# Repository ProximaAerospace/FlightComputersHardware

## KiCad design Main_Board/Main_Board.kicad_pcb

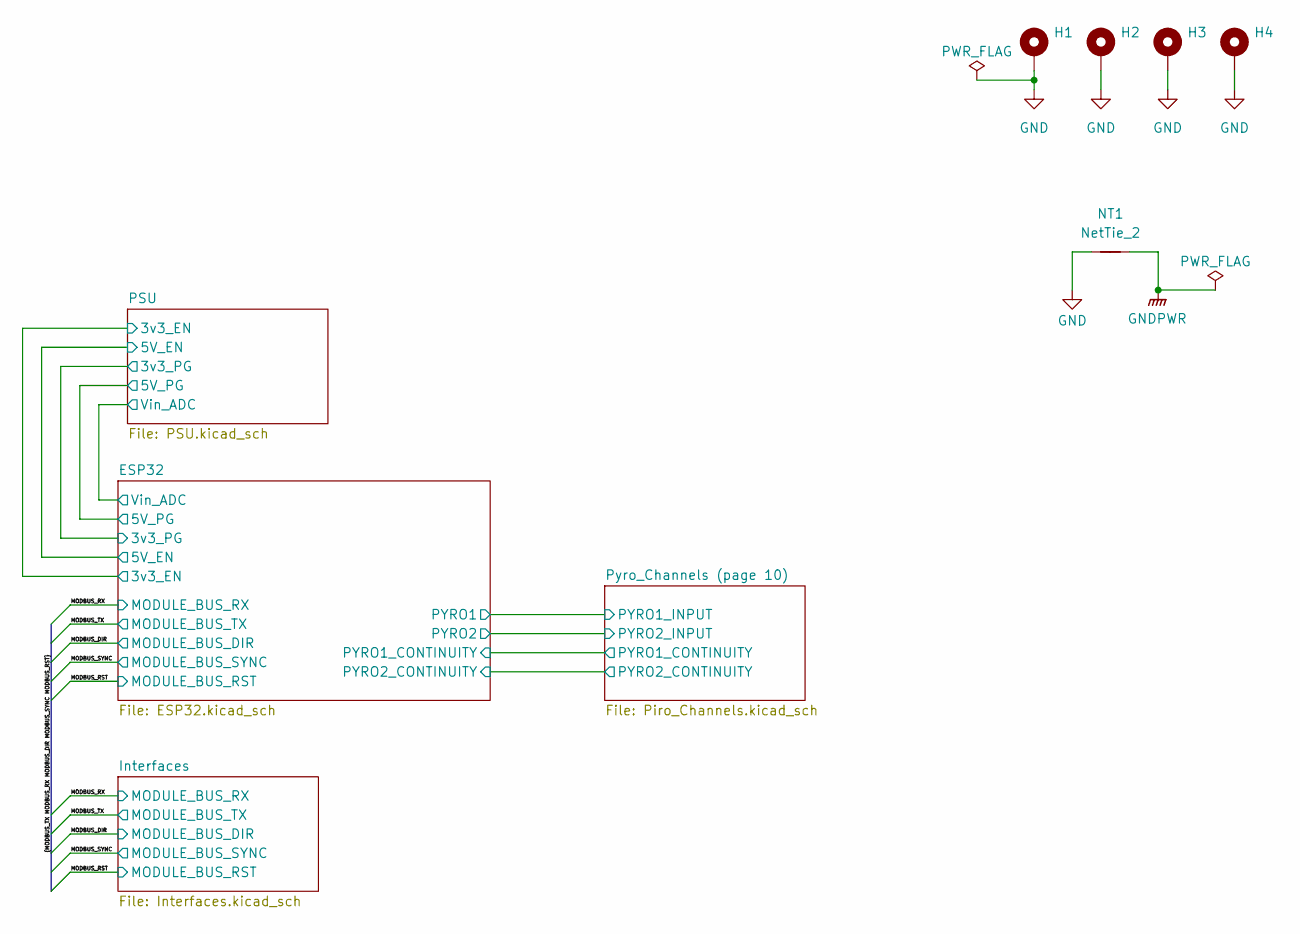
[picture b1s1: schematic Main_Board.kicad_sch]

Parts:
H1, H2: MountingHole_Pad; MountingHole_3.2mm_M3_DIN965_Pad_TopBottom
H3, H4: MountingHole_Pad; MountingHole_2.2mm_M2
NT1: NetTie_2; NetTie-2_SMD_Pad2.0mm

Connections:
GND: H1.1 (1_1), H2.1 (1_1), H3.1, H4.1, NT1.1; also elsewhere on the board
GNDPWR: NT1.2; also elsewhere on the board

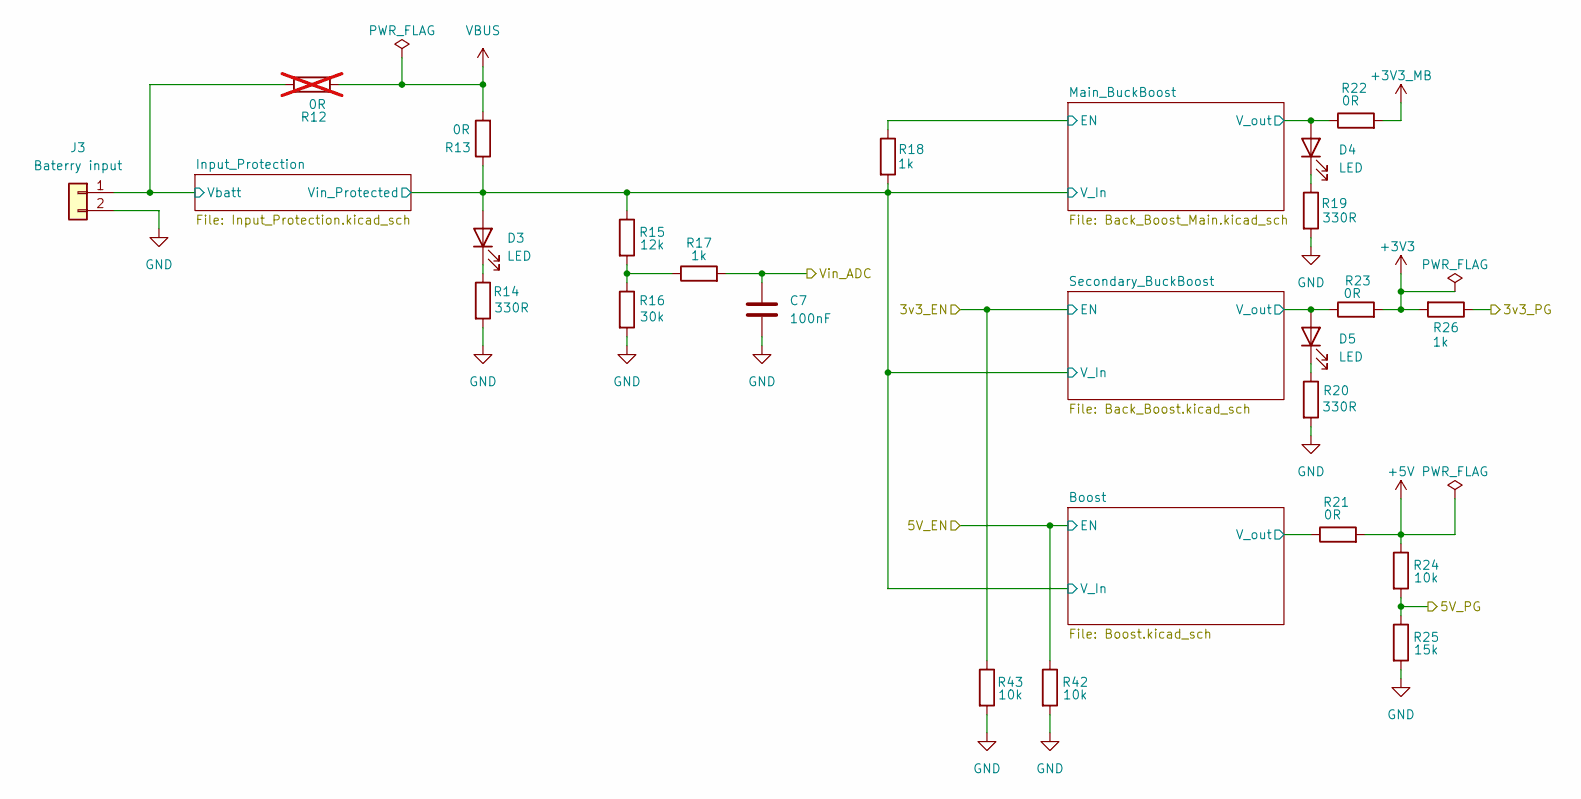
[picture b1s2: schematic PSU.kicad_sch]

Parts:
C7: 100nF; C_0603_1608Metric
D3, D4, D5: LED; D_0603_1608Metric
J3: Baterry input; JST_PH_B2B-PH-K_1x02_P2.00mm_Vertical
R12: 0R; R_0603_1608Metric; not fitted
R13: 0R; R_0805_2012Metric
R14, R19, R20: 330R; R_0603_1608Metric
R15: 12k; R_0603_1608Metric
R16: 30k; R_0603_1608Metric
R17, R18, R26: 1k; R_0603_1608Metric
R21, R22, R23: 0R; R_0603_1608Metric
R24, R42, R43: 10k; R_0603_1608Metric
R25: 15k; R_0603_1608Metric

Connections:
+3V3: R23.2, R26.2; also elsewhere on the board
+3V3_MB: R22.2; also elsewhere on the board
+5V: R21.2, R24.1; also elsewhere on the board
/ESP32/3v3_EN: R43.1; also elsewhere on the board
/ESP32/3v3_PG: R26.1; also elsewhere on the board
/ESP32/5V_EN: R42.1; also elsewhere on the board
/ESP32/5V_PG: R24.2, R25.1; also elsewhere on the board
/ESP32/Vin_ADC: C7.1, R17.2; also elsewhere on the board
/PSU/Boost/V_In: D3.2 (A), R13.1, R15.1, R18.2; also elsewhere on the board
/PSU/Boost/V_out: R21.1; also elsewhere on the board
/PSU/Input_Protection/Vbatt: J3.1, R12.2; also elsewhere on the board
/PSU/Main_BuckBoost/EN: R18.1; also elsewhere on the board
/PSU/Main_BuckBoost/V_out: D4.2 (A), R22.1; also elsewhere on the board
/PSU/Secondary_BuckBoost/V_out: D5.2 (A), R23.1; also elsewhere on the board
GND: C7.2, J3.2, R14.2, R16.2, R19.2, R20.2, R25.2, R42.2, R43.2; also elsewhere on the board
unnamed: D3.1 (K), R14.1
unnamed: D4.1 (K), R19.1
unnamed: D5.1 (K), R20.1
unnamed: R15.2, R16.1, R17.1
VBUS: R12.1, R13.2; also elsewhere on the board

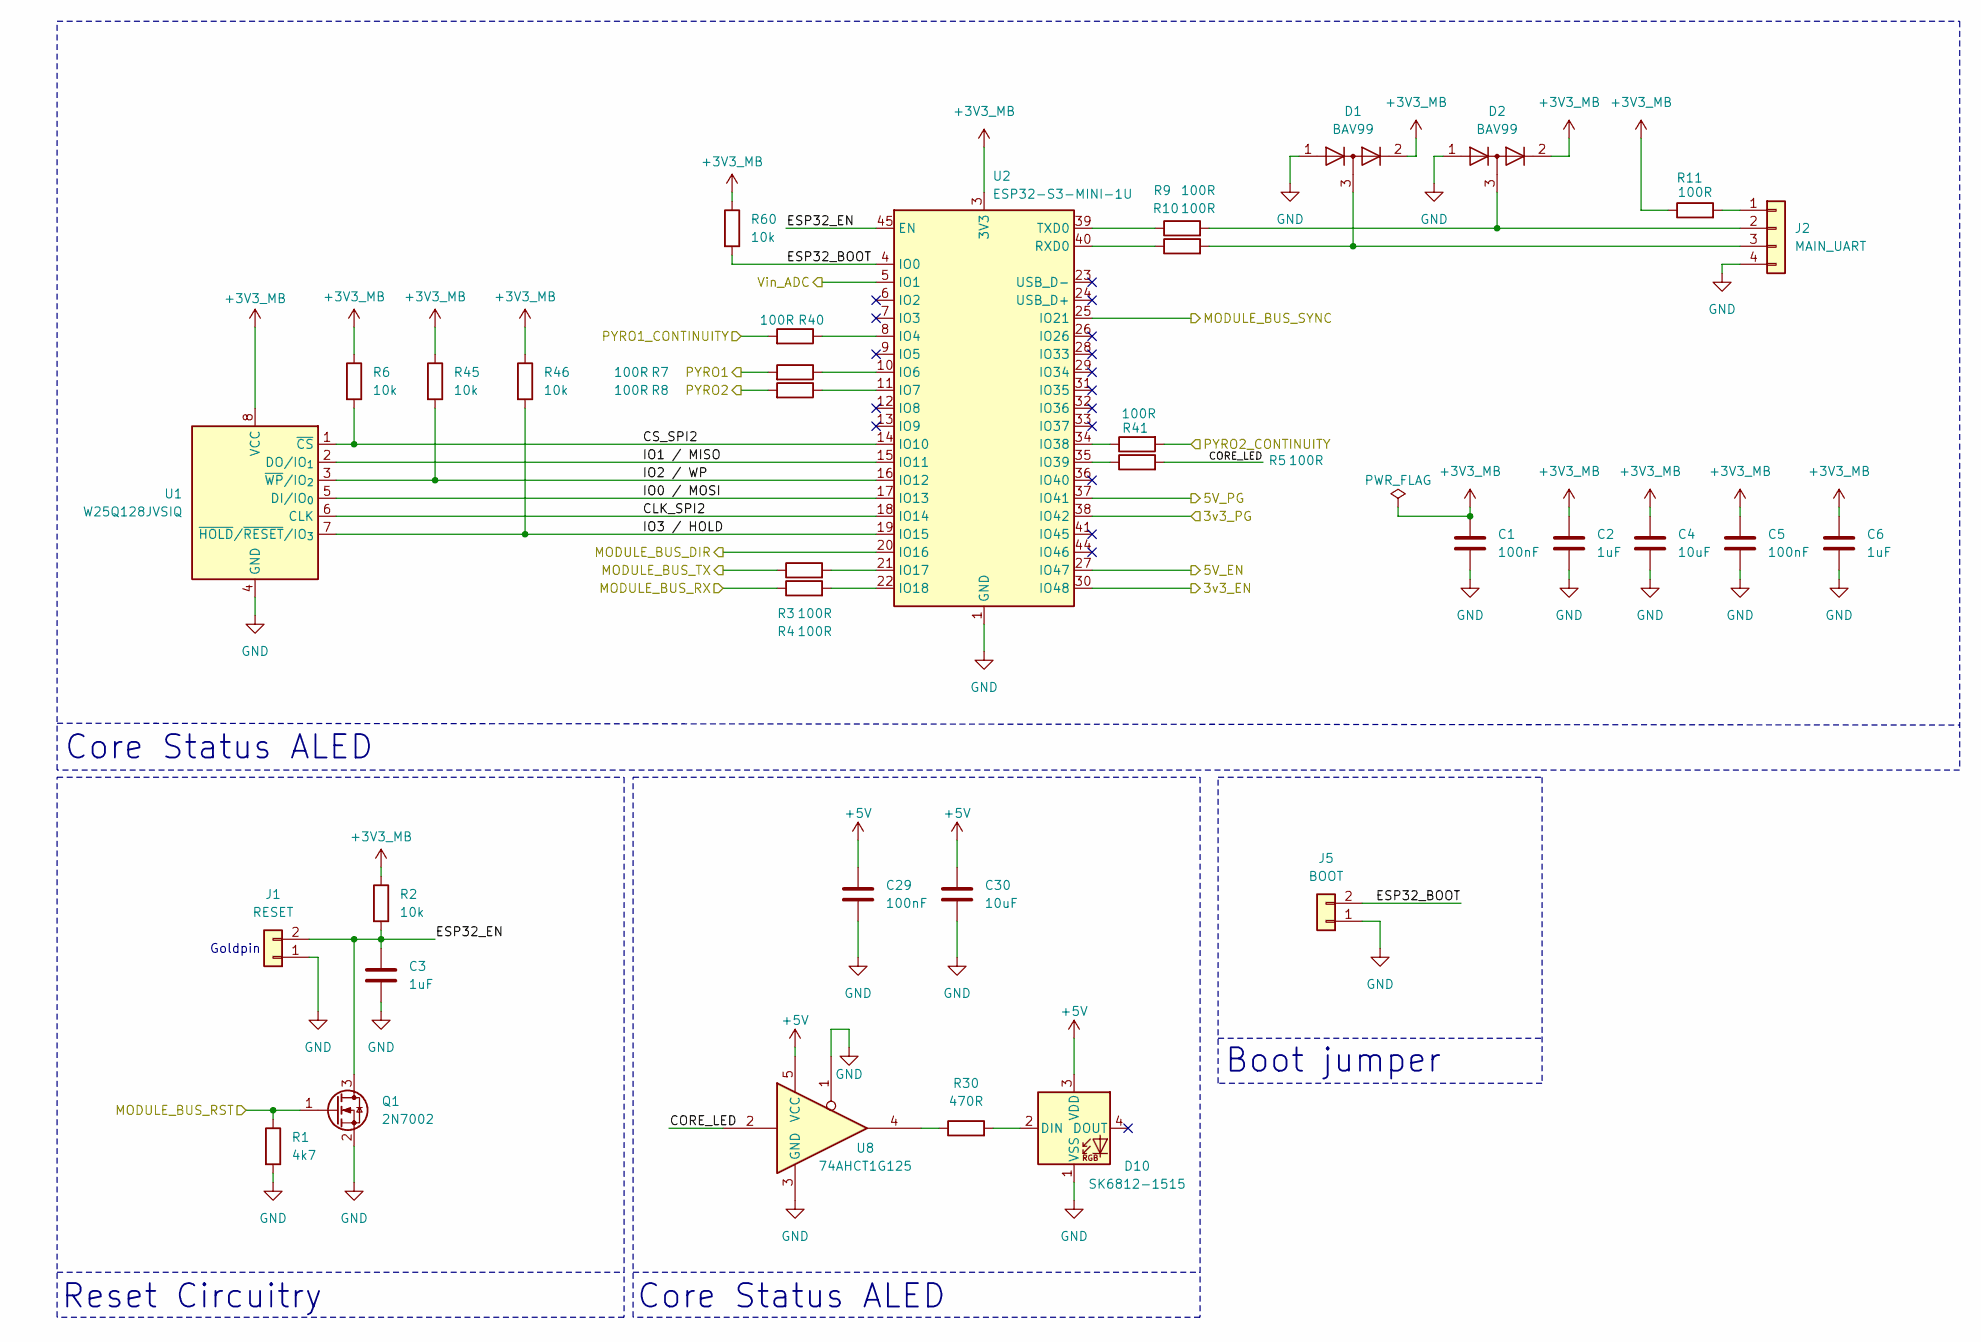
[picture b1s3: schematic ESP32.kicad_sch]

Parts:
C1, C5, C29: 100nF; C_0603_1608Metric
C2, C3, C6: 1uF; C_0603_1608Metric
C4, C30: 10uF; C_0603_1608Metric
D1, D2: BAV99; SOT-23
D10: SK6812-1515; sk68015-1515
J1: RESET; PinHeader_1x02_P1.27mm_Vertical
J2: MAIN_UART; PinHeader_1x04_P2.54mm_Vertical
J5: BOOT; PinHeader_1x02_P1.27mm_Vertical
Q1: 2N7002; SOT-23
R1: 4k7; R_0603_1608Metric
R2, R6, R45, R46, R60: 10k; R_0603_1608Metric
R3, R4, R5, R7, R8, R9, R10, R11, R40, R41: 100R; R_0603_1608Metric
R30: 470R; R_0603_1608Metric
U1: W25Q128JVSIQ; SOIC-8_5.3x5.3mm_P1.27mm
U2: ESP32-S3-MINI-1U
U8: 74AHCT1G125; SOT-353_SC-70-5

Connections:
+3V3_MB: C1.1, C2.1, C4.1, C5.1, C6.1, D1.2 (A), D2.2 (A), R2.1, R6.1, R11.1, R45.1, R46.1, R60.1, U1.8 (VCC), U2.3 (3V3); also elsewhere on the board
+5V: C29.1, C30.1, D10.3 (VDD), U8.5 (VCC); also elsewhere on the board
/ESP32/3v3_EN: U2.30 (IO48); also elsewhere on the board
/ESP32/3v3_PG: U2.38 (IO42); also elsewhere on the board
/ESP32/5V_EN: U2.27 (IO47); also elsewhere on the board
/ESP32/5V_PG: U2.37 (IO41); also elsewhere on the board
/ESP32/CLK_SPI2: U1.6 (CLK), U2.18 (IO14)
/ESP32/CORE_LED: R5.2, U8.2
/ESP32/CS_SPI2: R6.2, U1.1 (~CS), U2.14 (IO10)
/ESP32/ESP32_BOOT: J5.2, R60.2, U2.4 (IO0)
/ESP32/ESP32_EN: C3.1, J1.2, Q1.3 (D), R2.2, U2.45 (EN)
/ESP32/IO0 / MOSI: U1.5 (DI/IO_{0}), U2.17 (IO13)
/ESP32/IO1 / MISO: U1.2 (DO/IO_{1}), U2.15 (IO11)
/ESP32/IO2 / WP: R45.2, U1.3 (~WP/IO_{2}), U2.16 (IO12)
/ESP32/IO3 / HOLD: R46.2, U1.7 (~HOLD/~RESET/IO_{3}), U2.19 (IO15)
/ESP32/PYRO1: R7.2; also elsewhere on the board
/ESP32/PYRO1_CONTINUITY: R40.2; also elsewhere on the board
/ESP32/PYRO2: R8.2; also elsewhere on the board
/ESP32/PYRO2_CONTINUITY: R41.2; also elsewhere on the board
/ESP32/Vin_ADC: U2.5 (IO1); also elsewhere on the board
/MODBUS_DIR: U2.20 (IO16); also elsewhere on the board
/MODBUS_RST: Q1.1 (G), R1.1; also elsewhere on the board
/MODBUS_RX: R4.1; also elsewhere on the board
/MODBUS_SYNC: U2.25 (IO21); also elsewhere on the board
/MODBUS_TX: R3.1; also elsewhere on the board
GND: C1.2, C2.2, C3.2, C4.2, C5.2, C6.2, C29.2, C30.2, D1.1 (K), D2.1 (K), D10.1 (VSS), J1.1, J2.4, J5.1, Q1.2 (S), R1.2, U1.4 (GND), U2.1 (GND), U2.2 (GND), U2.42 (GND), U2.43 (GND), U2.46 (GND), U2.47 (GND), U2.48 (GND), U2.49 (GND), U2.50 (GND), U2.51 (GND), U2.52 (GND), U2.53 (GND), U2.54 (GND), U2.55 (GND), U2.56 (GND), U2.57 (GND), U2.58 (GND), U2.59 (GND), U2.60 (GND), U2.61 (GND), U2.62 (GND), U2.63 (GND), U2.64 (GND), U2.65 (GND), U8.1, U8.3 (GND); also elsewhere on the board
unnamed: D10.2 (DIN), R30.2
unnamed: J2.1, R11.2
unnamed: D2.3 (K), J2.2, R9.2
unnamed: D1.3 (K), J2.3, R10.2
unnamed: R30.1, U8.4
unnamed: R40.1, U2.8 (IO4)
unnamed: R7.1, U2.10 (IO6)
unnamed: R8.1, U2.11 (IO7)
unnamed: R3.2, U2.21 (IO17)
unnamed: R4.2, U2.22 (IO18)
unnamed: R41.1, U2.34 (IO38)
unnamed: R5.1, U2.35 (IO39)
unnamed: R10.1, U2.40 (RXD0)
unnamed: R9.1, U2.39 (TXD0)

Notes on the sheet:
Reset Circuitry
Goldpin
Core Status ALED
Boot jumper

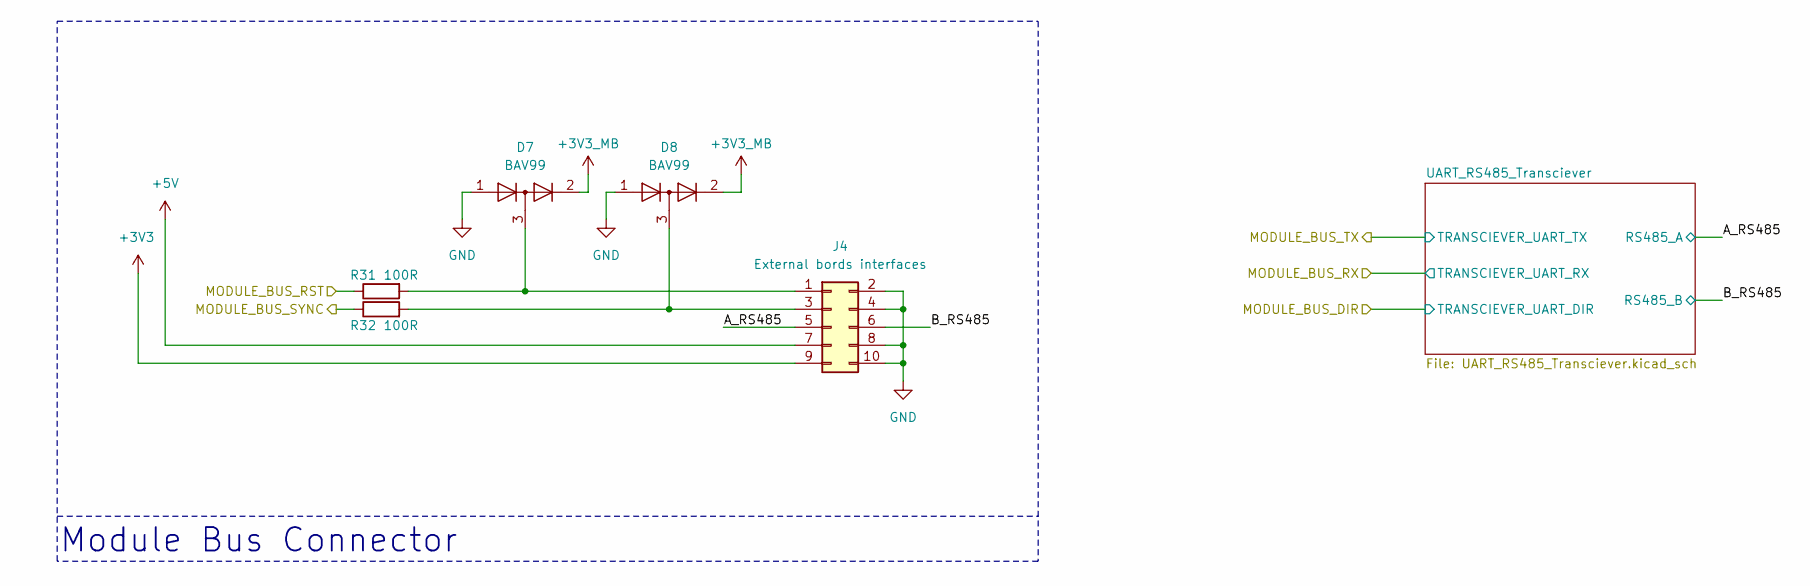
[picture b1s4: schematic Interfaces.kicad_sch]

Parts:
D7, D8: BAV99; SOT-23
J4: External bords interfaces; PinHeader_2x05_P1.27mm_Vertical
R31, R32: 100R; R_0603_1608Metric

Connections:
+3V3: J4.9; also elsewhere on the board
+3V3_MB: D7.2 (A), D8.2 (A); also elsewhere on the board
+5V: J4.7; also elsewhere on the board
/Interfaces/A_RS485: J4.5; also elsewhere on the board
/Interfaces/B_RS485: J4.6; also elsewhere on the board
/MODBUS_RST: R31.1; also elsewhere on the board
/MODBUS_SYNC: R32.1; also elsewhere on the board
GND: D7.1 (K), D8.1 (K), J4.2, J4.4, J4.8, J4.10; also elsewhere on the board
unnamed: D7.3 (K), J4.1, R31.2
unnamed: D8.3 (K), J4.3, R32.2

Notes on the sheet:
Module Bus Connector

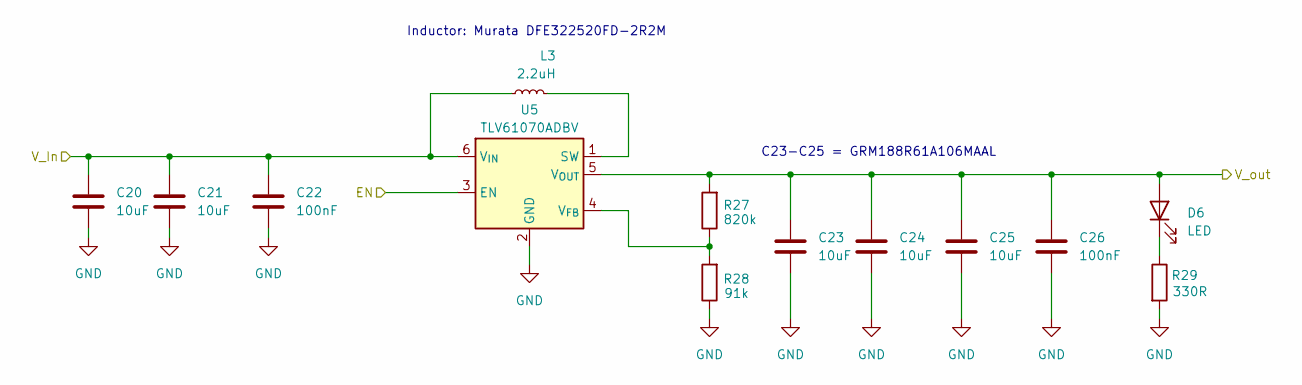
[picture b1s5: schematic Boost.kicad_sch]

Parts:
C20, C21, C23, C24, C25: 10uF; C_0603_1608Metric
C22, C26: 100nF; C_0603_1608Metric
D6: LED; D_0603_1608Metric
L3: 2.2uH; L_1210_3225Metric
R27: 820k; R_0603_1608Metric
R28: 91k; R_0603_1608Metric
R29: 330R; R_0603_1608Metric
U5: TLV61070ADBV; SOT-23-6

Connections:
/ESP32/5V_EN: U5.3 (EN); also elsewhere on the board
/PSU/Boost/V_In: C20.1, C21.1, C22.1, L3.2, U5.6 (V_{IN}); also elsewhere on the board
/PSU/Boost/V_out: C23.1, C24.1, C25.1, C26.1, D6.2 (A), R27.2, U5.5 (V_{OUT}); also elsewhere on the board
GND: C20.2, C21.2, C22.2, C23.2, C24.2, C25.2, C26.2, R28.1, R29.2, U5.2 (GND); also elsewhere on the board
unnamed: D6.1 (K), R29.1
unnamed: L3.1, U5.1 (SW)
unnamed: R27.1, R28.2, U5.4 (V_{FB})

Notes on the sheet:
Inductor: Murata DFE322520FD-2R2M
C23-C25 = GRM188R61A106MAAL

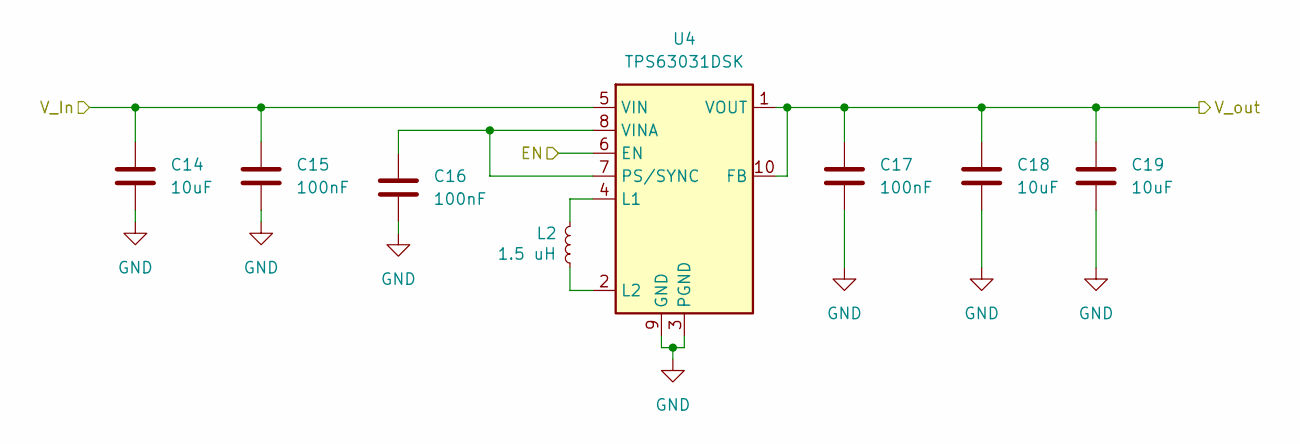
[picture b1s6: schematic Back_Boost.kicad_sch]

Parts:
C14, C18, C19: 10uF; C_0603_1608Metric
C15, C16, C17: 100nF; C_0603_1608Metric
L2: 1.5 uH; L_Taiyo-Yuden_MD-3030
U4: TPS63031DSK; WSON-10-1EP_2.5x2.5mm_P0.5mm_EP1.2x2mm

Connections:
/ESP32/3v3_EN: U4.6 (EN); also elsewhere on the board
/PSU/Boost/V_In: C14.1, C15.1, U4.5 (VIN); also elsewhere on the board
/PSU/Secondary_BuckBoost/V_out: C17.1, C18.1, C19.1, U4.1 (VOUT), U4.10 (FB); also elsewhere on the board
GND: C14.2, C15.2, C16.2, C17.2, C18.2, C19.2, U4.3 (PGND), U4.9 (GND), U4.11 (PGND); also elsewhere on the board
unnamed: L2.1, U4.4 (L1)
unnamed: L2.2, U4.2 (L2)
unnamed: C16.1, U4.7 (PS/SYNC), U4.8 (VINA)

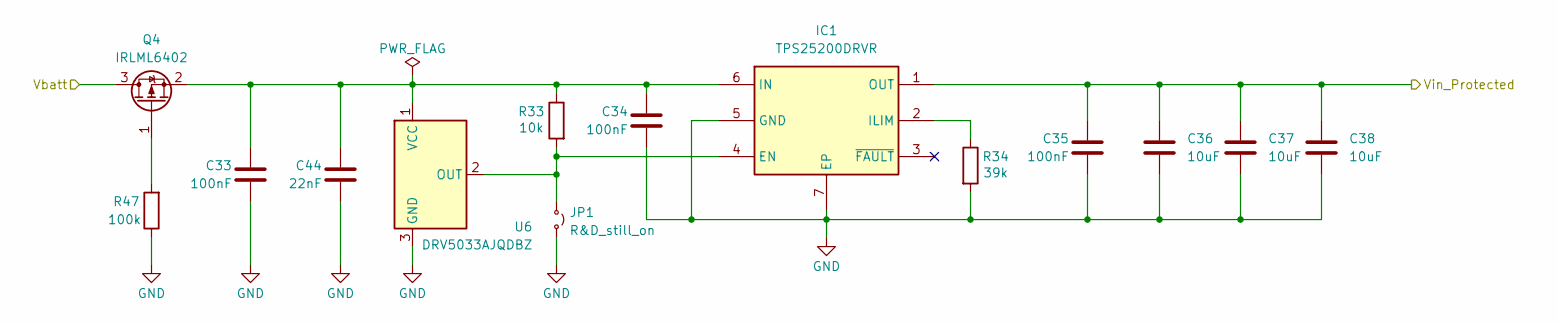
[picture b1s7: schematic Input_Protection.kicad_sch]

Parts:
C33, C34, C35: 100nF; C_0603_1608Metric
C36, C37, C38: 10uF; C_0603_1608Metric
C44: 22nF; C_0603_1608Metric
IC1: TPS25200DRVR; SON65P200X200X80-7N; Manufacturer_Part_Number TPS25200DRVR; Mouser Part Number 595-TPS25200DRVR
JP1: R&D_still_on; SolderJumper-2_P1.3mm_Open_RoundedPad1.0x1.5mm
Q4: IRLML6402; SOT-23
R33: 10k; R_0603_1608Metric
R34: 39k; R_0603_1608Metric
R47: 100k; R_0603_1608Metric
U6: DRV5033AJQDBZ; SOT-23

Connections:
/PSU/Boost/V_In: C35.1, C36.1, C37.1, C38.1, IC1.1 (OUT); also elsewhere on the board
/PSU/Input_Protection/Vbatt: Q4.3 (D); also elsewhere on the board
GND: C33.2, C34.2, C35.2, C36.2, C37.2, C38.2, C44.2, IC1.5 (GND), IC1.7 (EP), JP1.2 (B), R34.2, R47.1, U6.3 (GND); also elsewhere on the board
unnamed: IC1.4 (EN), JP1.1 (A), R33.2, U6.2 (OUT)
unnamed: IC1.2 (ILIM), R34.1
unnamed: C33.1, C34.1, C44.1, IC1.6 (IN), Q4.2 (S), R33.1, U6.1 (VCC)
unnamed: Q4.1 (G), R47.2

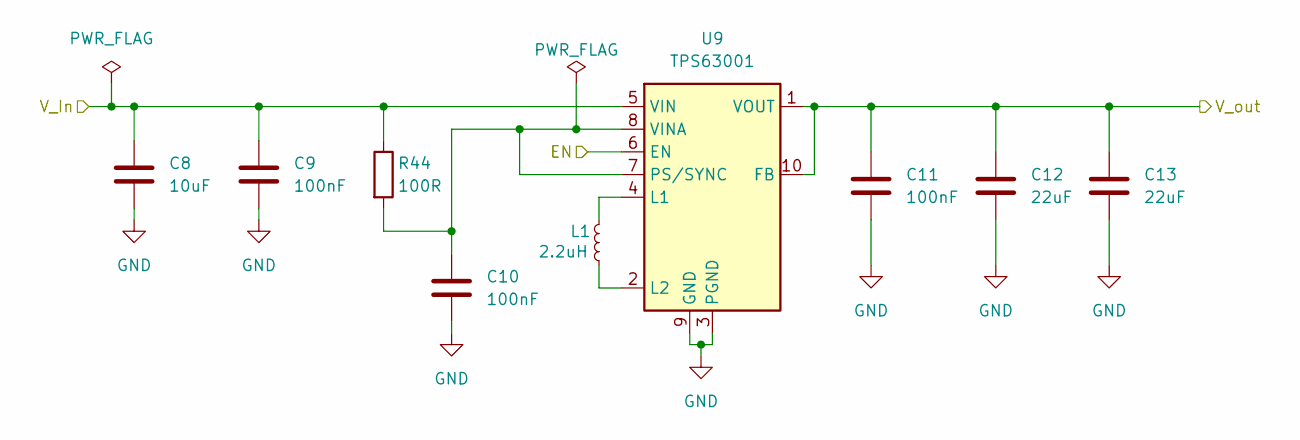
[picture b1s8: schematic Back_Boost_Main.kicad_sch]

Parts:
C8: 10uF; C_0603_1608Metric
C9, C10, C11: 100nF; C_0603_1608Metric
C12, C13: 22uF; C_0603_1608Metric
L1: 2.2uH; L_Taiyo-Yuden_MD-3030
R44: 100R; R_0603_1608Metric
U9: TPS63001; Texas_DRC0010J_ThermalVias

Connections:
/PSU/Boost/V_In: C8.1, C9.1, R44.1, U9.5 (VIN); also elsewhere on the board
/PSU/Main_BuckBoost/EN: U9.6 (EN); also elsewhere on the board
/PSU/Main_BuckBoost/V_out: C11.1, C12.1, C13.1, U9.1 (VOUT), U9.10 (FB); also elsewhere on the board
GND: C8.2, C9.2, C10.2, C11.2, C12.2, C13.2, U9.3 (PGND), U9.9 (GND), U9.11 (PGND); also elsewhere on the board
unnamed: L1.1, U9.4 (L1)
unnamed: L1.2, U9.2 (L2)
unnamed: C10.1, R44.2, U9.7 (PS/SYNC), U9.8 (VINA)

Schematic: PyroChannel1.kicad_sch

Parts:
C42: 470uF; CP_Elec_8x10
J7: Terminal; SHDR2W80P0X381_1X2_841X700X920P
Q7: MMBT3904LT1G; SOT-23
Q8: FDN339AN; SOT-23
R50, R53: 10k; R_0603_1608Metric
R51: 100k; R_0603_1608Metric
R52: 1k; R_0603_1608Metric
R54: 47k; R_0603_1608Metric

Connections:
+3V3_MB: R50.2; also elsewhere on the board
/ESP32/PYRO1: R52.1; also elsewhere on the board
/ESP32/PYRO1_CONTINUITY: Q7.3 (C), R50.1; also elsewhere on the board
GND: Q7.2 (E), R51.1; also elsewhere on the board
GNDPWR: C42.2, Q8.2 (S), R53.1; also elsewhere on the board
unnamed: J7.2, Q8.3 (D), R54.2
unnamed: Q7.1 (B), R51.2, R54.1
unnamed: Q8.1 (G), R52.2, R53.2
VBUS: C42.1, J7.1; also elsewhere on the board

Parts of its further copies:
C43: 470uF; CP_Elec_8x10
J8: Terminal; SHDR2W80P0X381_1X2_841X700X920P
Q9: MMBT3904LT1G; SOT-23
Q10: FDN339AN; SOT-23
R55, R58: 10k; R_0603_1608Metric
R56: 100k; R_0603_1608Metric
R57: 1k; R_0603_1608Metric
R59: 47k; R_0603_1608Metric

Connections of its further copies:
+3V3_MB: R55.2; also elsewhere on the board
/ESP32/PYRO2: R57.1; also elsewhere on the board
/ESP32/PYRO2_CONTINUITY: Q9.3 (C), R55.1; also elsewhere on the board
GND: Q9.2 (E), R56.1; also elsewhere on the board
GNDPWR: C43.2, Q10.2 (S), R58.1; also elsewhere on the board
unnamed: J8.2, Q10.3 (D), R59.2
unnamed: Q9.1 (B), R56.2, R59.1
unnamed: Q10.1 (G), R57.2, R58.2
VBUS: C43.1, J8.1; also elsewhere on the board

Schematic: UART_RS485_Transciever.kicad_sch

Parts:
C39: 1uF; C_0603_1608Metric
C40, C41: 100nF; C_0603_1608Metric
D12: SM712_SOT23; SOT-23
R35, R36: 10k; R_0603_1608Metric
R37, R38: 10R; R_0603_1608Metric
R39: 120R; R_0603_1608Metric
U7: THVD1450DRBR; VSON-8-1EP_3x3mm_P0.65mm_EP1.6x2.4mm

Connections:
+3V3_MB: C39.1, C40.1, C41.1, R35.1, U7.8 (VCC); also elsewhere on the board
/Interfaces/A_RS485: D12.1 (A1), R37.1, R39.1; also elsewhere on the board
/Interfaces/B_RS485: D12.2 (A2), R38.2, R39.2; also elsewhere on the board
/MODBUS_DIR: R36.1, U7.2 (~RE), U7.3 (DE); also elsewhere on the board
/MODBUS_RX: R35.2, U7.1 (RO); also elsewhere on the board
/MODBUS_TX: U7.4 (DI); also elsewhere on the board
GND: C39.2, C40.2, C41.2, D12.3 (common), R36.2, U7.5 (GND), U7.9 (PAD); also elsewhere on the board
unnamed: R37.2, U7.6 (A)
unnamed: R38.1, U7.7 (B)

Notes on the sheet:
Add DIP switches on modules to toggle the 120 ohm termination resistor on the bus

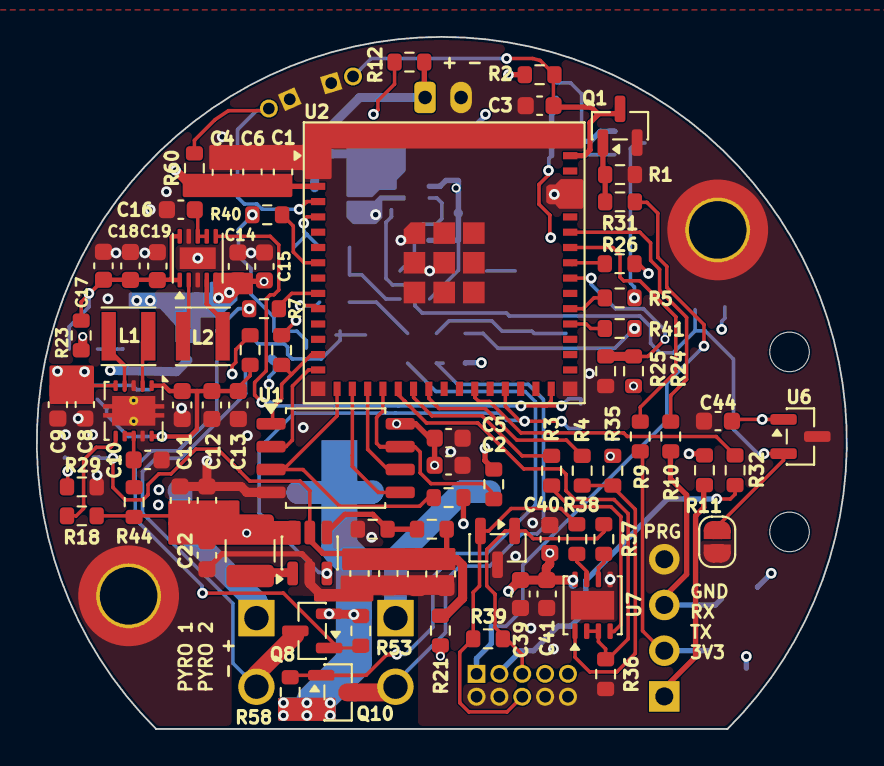
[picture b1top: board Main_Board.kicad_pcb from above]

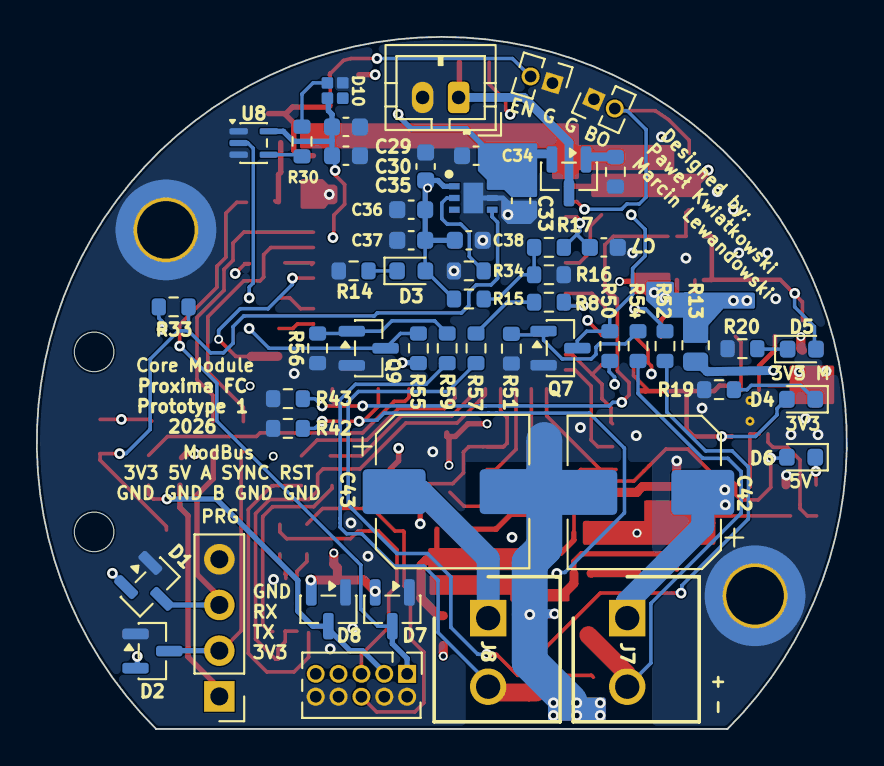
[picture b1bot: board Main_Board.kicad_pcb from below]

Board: 4 copper layers, 45.0 x 38.4 mm, 139 parts (55 on the bottom side), 78 nets.
